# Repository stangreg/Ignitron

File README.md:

An ESP32 based foot pedal to communicate with the Spark Amp and Spark App via Bluetooth LE (iOS) and Bluetooth Serial (Android). Also works as a control device for a Looper app on the mobile. Ignitron also supports the built-in looper and additional HW presets of Spark 2.

**Ignitron has been successfully tested with**

* Spark 2
* Spark 40
* Spark Mini
* Spark GO
* **Spark NEO**

**Ignitron** gives you full control over your Spark Amp:
* Switch between the four **hardware presets**
* Switch between **custom saved presets** organized in banks
* **Toggle effects** for the selected preset
* **Save new presets** to Ignitron via the Spark App
* **Delete** stored presets
* Control the **Spark 2 internal looper**. 
* Control **Looper apps** on a mobile (actually *all* apps which support bluetooth keyboard controls)
* Use the built-in **Tuner**
* Show **Input Volume**
* Multiple BT keyboard layouts configurable

Adding new presets to **Ignitron** can easily be done as it can also act like a Spark Amp. Simply connect to **Ignitron** with the Spark App and save new presets directly from ToneCloud (or your downloaded presets) to **Ignitron**.

One big advantage of **Ignitron** is that it communicates with the Spark Amp using the **Bluetooth LE** protocol.
This means it is possible to connect your mobile to your Spark Amp as an audio speaker and play along your favorite songs while you control your effects with Ignitron.

The current active preset and effects are indicated via LEDs.\
In addition, the **built-in display** provides information on
* selected bank and preset number
* selected preset name
* operation mode (Preset, Manual/FX, Looper)
* activated pedal types in the FX chain
* Bluetooth connection status to Spark Amp and Spark App

This work was inspired by the [Sparkpal project](https://github.com/jamesguitar3/sparkpal), and the [Python Spark Parser project](https://github.com/paulhamsh/Spark-Parser) helped me to understand the messages being sent to and from the Spark Amp.

The following sections show how to [build](https://github.com/stangreg/SparkBLE#Building-Ignitron) and [operate](https://github.com/stangreg/SparkBLE#Operating-Ignitron) Ignitron.

Do you like my project? Then you can [buy me a coffee](https://ko-fi.com/stangreg)

# Building Ignitron
Software: [click here](https://github.com/stangreg/Ignitron/blob/main/src/)

Hardware: [click here](https://github.com/stangreg/Ignitron/blob/main/hardware/)

# Operating Ignitron

## Table of contents
* [Operation modes](https://github.com/stangreg/SparkBLE#operation-modes)
* [APP mode](https://github.com/stangreg/SparkBLE#app-mode)
* [Keyboard mode](https://github.com/stangreg/SparkBLE#keyboard-mode)
* [AMP mode](https://github.com/stangreg/SparkBLE#amp-mode)
  * [Storing a new preset](https://github.com/stangreg/SparkBLE#storing-a-new-preset-a-preset-from-the-app-needs-to-be-loaded)
  * [Deleting an existing preset](https://github.com/stangreg/SparkBLE#deleting-a-preset-only-possible-with-no-preset-from-the-app-loaded)
  * [Manually creating presets](https://github.com/stangreg/SparkBLE#manually-creating-presets)
    * [Preset format](https://github.com/stangreg/SparkBLE#preset-format)
    * [FX parameter reference](https://github.com/stangreg/SparkBLE#fx-parameter-reference)
* [OTA Update](https://github.com/stangreg/SparkBLE#OTA-Update)

## Operation modes
**Ignitron** has two operation modes, **APP mode** and **AMP mode**.\
In **APP mode** (default mode on startup), **Ignitron** connects to a Spark Amp and behaves like the Spark App towards the Spark Amp. It can then be used to switch between saved presets, toggle FX pedals, and even connect it to a Looper app on a mobile (providing 6 buttons to control a (looper or tabs) app).

**AMP mode** can be used to manage the presets stored on **Ignitron**, presets can be saved via the app or be deleted from **Ignitron**. For Android, the Bluetooth mode has to be set to Serial (SRL), for iOS it has to be set to BLE.\

**Keyboard mode** is useful when Ignitron should act as a bluetooth keyboard control without controlling a Spark Amp. This provides 2x6=12 buttons to control any supporting app (e.g., a looper or a tabs app).

To enter **AMP mode**, hold the `Preset 1` button during startup.
To enter **Keyboard mode**, hold the `Preset 3` button during startup.

Amp mode and Keyboard mode can best be started by holding the respective button pressed while pressing and holding `Preset 2` button to reset.

A graphical overview of all modes with button mapping can be found [here](https://github.com/stangreg/Ignitron/blob/main/resources/ignitron-cheatsheet.pdf). (Thanks to [@itarozzi](https://www.github.com/itarozzi) for creating this.)

## APP mode
In APP mode, the foot switches can be used to either switch between pre-saved presets (**Preset mode**), control all single effects in the selected preset (**Manual/FX mode**), or switch between presets while controlling an app on your mobile, e.g. a Looper app (**Looper (keyboard) mode**). If connected to a Spark 2 amp, the **Looper (amp) mode** will control the internal looper of the amp. You can easily toggle between **Preset mode** and **Manual/FX mode** by long pressing the `Bank-Up` button. To toggle between **Preset mode** and **Looper mode**, simply long-press the `Preset 4` button.

When selecting **Preset mode**, four buttons are used to select presets, the other two buttons are used to navigate through the preset banks. This way the user has access to a huge number of saved presets. When pressing the foot switch of the current active preset, the effect configured in the DRIVE section can be toggled.\
In **Manual/FX mode**, the user has direct access to all effects of the selected preset. Pressing a switch will toggle the respective FX type.\
When the **Tuner** is switched on, the output is shown on the display and the LEDs, allowing for quick tuning while connected with the amp.\
When **Looper (Keyboard) mode** is activated, Ignitron acts partially like a bluetooth keyboard. You can use the buttons to control a looper app, e.g. Loopy HD, and also switch between stored presets by long pressing the `Bank down`/`Bank up` buttons. **Note:** When switching presets in Looper mode, it will do this across banks.  
When **Looper (Amp) mode** is activated, Ignitron will control the internal looper of the Spark 2 amp. The display will also show information on the looper settings and click. The amp looper settings can easily be changed using Ignitron.

### Button commands in APP mode:

#### Preset mode
|Button      | Press pattern | Function           |
|----------- | :-----------: | ------------------ |
|`Bank down` | Short         | Navigate bank up   |
|`Bank up`   | Short         | Navigate bank down |
|`Preset 1`  | Short         | Select preset 1 / Toggle Drive |
|`Preset 2`  | Short         | Select preset 2 / Toggle Drive |
|`Preset 3`  | Short         | Select preset 3 / Toggle Drive |
|`Preset 4`  | Short         | Select preset 4 / Toggle Drive |
|`Preset 4` | Long           | Switch to Looper mode |
|`Bank down`   | Long          | Switch to Tuner mode. Short press while in Tuner mode to switch back to Preset mode.  |
|`Bank up`   | Long          | Switch to FX mode  |
|`Preset 2`  | Long          | Restart **Ignitron**  |

#### Manual/FX mode
|Button      | Press pattern | Function              |
|----------- | :-----------: | --------------------- |
|`Bank down` | Short         | Toggle Noise Gate     |
|`Bank up`   | Short         | Toggle Compressor/Wah |
|`Preset 1`  | Short         | Toggle Drive          |
|`Preset 2`  | Short         | Toggle Modulation     |
|`Preset 3`  | Short         | Toggle Delay          |
|`Preset 4`  | Short         | Toggle Reverb         |
|`Bank up`   | Long          | Switch to Preset mode |
|`Preset 2`  | Long          | Restart **Ignitron**  |

#### Looper (keyboard) mode (combined with Preset functionality)
|Button      | Press pattern | Function           |
|----------- | :-----------: | ------------------ |
|`Preset 1`  | Short         | Sends character "1" (can be freely configured in app) |
|`Preset 2`  | Short         | Sends character "2" (can be freely configured in app) |
|`Preset 3`  | Short         | Sends character "3" (can be freely configured in app) |
|`Preset 4`  | Short         | Sends character "4" (can be freely configured in app) |
|`Bank down` | Short         | Sends character "5" (can be freely configured in app) |
|`Bank up`   | Short         | Sends character "6" (can be freely configured in app) |
|`Bank down` | Long          | Switch to previous preset (across banks)  |
|`Bank up` | Long          | Switch to next preset (across banks)  |
|`Preset 4` | Long          | Switch to Preset mode |
|`Preset 2`  | Long          | Restart **Ignitron**     |

***Note:*** *In Looper mode, Ignitron is connected to your mobile as a bluetooth keyboard. If supported by the respective app on the mobile, the buttons can be freely configured to any function offered by the respective App. You may need to manually connect to the Ignitron BLE keyboard in your Bluetooth settings after switching to Looper mode.*

Example Button setup (available commands depend on availability in the respective app):
|Button      | Function           |
|----------- | ------------------ |
|`Preset 1`  | Record/overdub current track |
|`Preset 2`  | Play/pause session |
|`Preset 3`  | Delete current track (press twice) |
|`Preset 4`  | Mute current track |
|`Bank down` | Switch to previous track |
|`Bank up`   | Switch to next track |

#### Looper (amp) mode (to control the Spark 2 looper)
The preset buttons 1-3 mimick the three looper buttons on the amp, the LED status should match the LEDs on the amp.
With long pressing the `Bank up` button, Ignitron will toggle between Looper control mode and Looper config mode. The current mode will be shown by a 'L' or 'C' in the display respectively.

**Looper control mode**
|Button      | Press pattern | Function           |
|----------- | :-----------: | ------------------ |
|`Preset 1`  | Short         | Record / Dub |
|`Preset 2`  | Short         | Play / Stop |
|`Preset 3`  | Short         | Undo / Redo |
|`Preset 4`  | Short         | Read current Record status from amp (only needed for analysis) |
|`Bank down` | Short         | Tap tempo (repeatedly press button to adjust the tempo) |
|`Bank up`   | Short         | Read current looper settings from amp (only needed for analysis) |
|`Preset 3` | Long          | Delete all loops (reset)  |
|`Bank up` | Long          | Change to **Looper Config** mode  |
|`Preset 4` | Long          | Switch to Preset mode |
|`Preset 2`  | Long          | Restart **Ignitron**     |

**Looper config mode**
|Button      | Press pattern | Function           |
|----------- | :-----------: | ------------------ |
|`Preset 1`  | Short         | Change number of bars to be recorded |
|`Preset 2`  | Short         | Change feel of loop (straight / shuffle) |
|`Preset 3`  | Short         | Enable / Disable click |
|`Preset 4`  | Short         | NO FUNCTION |
|`Bank down` | Short         | Tap tempo (repeatedly press button to adjust the tempo) |
|`Bank up`   | Short         | NO FUNCTION |
|`Bank up` | Long          | Change to **Looper Control** mode  |
|`Preset 4` | Long          | Switch to Preset mode |
|`Preset 2`  | Long          | Restart **Ignitron**     |

-----------------------------------------------

## Keyboard mode
This mode will turn the Ignitron into a Bluetooth LE keyboard. All buttons will act like keyboard presses, there is no functionality regarding Preset change or other Spark Amp related functions. Use this mode if you want to only use Ignitron as a looper control device (or any other supporting app like a tabs app) . If you want to use looper control in combination with Spark Amp control, use the Looper mode as part of the APP mode (see above).
In the code, multiple different keyboard layouts can be defined to support various apps. In operations, Ignitron can switch between these keyboard with the press of a button.

Every key needs be configured with the following parameters:
- *Key ID* (1-6 for short presses, 11-14 for long presses)
- *Key code*
- *Modifier key* (Shift, CTRL, etc.)
- Key press *repetitions* (0 for single press)
- *String representation* of key in display (should only be 1 character)

In operations, when a button is pressed, the corresponding key including modifiers will be sent to the connected device. The display will show the key representations of the currently active keyboard.
The standard defined keyboard layout will send characters `1` to `6` for short presses and characters `A` to `D`for long presses.

Example:
```
{
  1,
  0xD8, // KEY_LEFT_ARROW
  0x81, // KEY_LEFT_SHIFT
  2,
  "<"
}
```
   
If a key is configured like the above, a button press will send the combination of the `LEFT SHIFT` and `LEFT ARROW` keys with 2 repetitions. In the display the key will be shown as `<`.
Long pressing `Bank down` and `Bank up` are reserved for keyboard layout switching.

Key codes for special keys can be found here: [BLE Keyboard Library](https://github.com/T-vK/ESP32-BLE-Keyboard/blob/master/BleKeyboard.h)

In keyboard mode, the following keys will be sent to the connected device:

|Button      | Press pattern | Function           |
|----------- | :-----------: | ------------------ |
|`Preset 1`  | Short         | Sends defined character (function can be freely configured in app) |
|`Preset 2`  | Short         | Sends defined character (function can be freely configured in app) |
|`Preset 3`  | Short         | Sends defined character (function can be freely configured in app) |
|`Preset 4`  | Short         | Sends defined character (function can be freely configured in app) |
|`Bank down` | Short         | Sends defined character (function can be freely configured in app) |
|`Bank up`   | Short         | Sends defined character (function can be freely configured in app) |
|`Preset 1`  | Long          | Sends defined character (function can be freely configured in app) |
|`Preset 2`  | Long          | Sends defined character (function can be freely configured in app) |
|`Preset 3`  | Long          | Sends defined character (function can be freely configured in app) |
|`Preset 4`  | Long          | Sends defined character (function can be freely configured in app) |
|`Bank down` | Long          | Switch to previous keyboard layout (cycling) |
|`Bank up`   | Long          | Switch to next keyboard layoout (cycling) |

-----------------------------------------------

## AMP mode
In AMP mode, **Ignitron** acts like a Spark AMP and can communicate with the Spark app running on a mobile. New presets can be stored on **Ignitron** and existing presets can be deleted.

### Connecting the Spark app with **Ignitron**

***Note:*** By default, Ignitron is configured to use BLE which only works with iOS. In order to connect an Android device, you need to switch to Serial Bluetooth. To do so, press and hold the `Bank Up` button when in AMP mode (after step 1. below). This will toggle the Bluetooth mode and restart **Ignitron**. After toggling the Bluetooth mode, start with step 1. below again. Ignitron persists the Bluetooth mode over restarts.  

1. Start **Ignitron** in AMP mode (hold `Preset 1` button during startup).
2. Open the Spark App on the mobile
3. For the first connection, make sure to have your real Spark Amp powered off to avoid the app connecting to it.
4. Hit the connect button in the app (or the + button in the connection overview)
5. Once the connection is established, you can give the connection a name in the app so you can distinguish from your regular Spark Amp connection.

### Storing a new preset (a preset from the app needs to be loaded)
1. Start **Ignitron** in AMP mode (hold Preset 1 button during startup).
2. Connect the Spark App with **Ignitron** (see above)
3. Select a preset in the app (either saved in the app or from ToneCloud).
4. The preset name should appear in the bottom line of the display
5. The `Preset`/`Bank` buttons on **Ignitron** can be used to navigate to the desired preset position.
6. Press the `Preset` button to mark the position for storing *(the LED of the selected preset position should start blinking)*
7. Hit the same `Preset` button a second time to confirm storage
(Hitting any other `Preset`/`Bank` button will revert the state back to navigating)
8. The preset will be saved to the selected position, other presets will be pushed one position back

#### Button commands (case: preset has been received from Spark app)
| Button     | Press pattern | Function                        | Remark |
| ---------- | :-----------: | ------------------------------- | ------ |
|`Bank down` | Short         | Navigate bank up                |        |
|`Bank up`   | Short         | Navigate bank down              |        |
|`Preset 1`  | Short         | Select preset 1                 | *Press twice to store received preset* |
|`Preset 2`  | Short         | Select preset 2                 | *Press twice to store received preset* |
|`Preset 3`  | Short         | Select preset 3                 | *Press twice to store received preset* |
|`Preset 4`  | Short         | Select preset 4                 | *Press twice to store received preset* |
|`Bank down` | Long          | Unload preset                   | *Removes loaded preset if present*     |
|`Bank up`   | Long          | Toggle Bluetooth mode                   | *Toggle between BLE and BT Serial mode*  |
|`Preset 2`  | Long          | Restart **Ignitron**                  |        |

### Deleting a preset (only possible when no preset from the app is loaded)
1. Start **Ignitron** in AMP mode (hold `Preset 1` button during startup).
2. Use the `Preset`/`Bank` buttons on **Ignitron** to navigate to the desired preset position
3. **Long press** the `Bank Down` button to mark the selected preset for deletion
4. The LED of the selected preset should start blinking
5. In the display you should see a prompt if deletion should be executed
6. If you want to cancel the deletion, simply short press any other button
7. Otherwise, **long press** the `Bank Down` button again to confirm deletion.
(Hitting any other button will cancel the deletion and return back to navigation)

#### Button commands (case: no preset has been received, slot is empty)
| Button     | Press pattern | Function                 | Remark |
| ---------- | :-----------: | ------------------------ | ------ |
|`Bank down` | Short         | Navigate bank up         |        |
|`Bank up`   | Short         | Navigate bank down       |        |
|`Preset 1`  | Short         | Select preset 1          |        |
|`Preset 2`  | Short         | Select preset 2          |        |
|`Preset 3`  | Short         | Select preset 3          |        |
|`Preset 4`  | Short         | Select preset 4          |        |
|`Bank down` | Long          | Mark preset for deletion | *Pressing any other button in that state will cancel the deletion* |
|`Bank down` | Long          | Delete marked preset     | *Only if preset was first marked for deletion* |
|`Bank up` | Long          | Toggle Bluetooth mode                   | *Toggle between BLE and BT Serial mode*  |
|`Preset 2`  | Long          | Restart **Ignitron**           |        |

-------------------------------------------------------

### Manually creating presets
*This method is only recommended if a preset cannot be transferred via the Spark app or if the preset files have been received/generated in a different way.*
1. Create a **preset file** in JSON format as shown below
2. Make sure the **file name** does not exceed 31 characters (including the `.json` suffix)
3. Put the file name into the **data folder**
4. Insert the file name (including the `.json` suffix) to the desired prefix location in the `PresetList.txt` file
5. *Place the PresetList.txt file into the data folder (if not already there)*
6. **Upload the data folder** to **Ignitron** via the Arduino IDE (or other tools)

#### Preset format
**Ignitron** stores presets in a JSON format using the SPIFFS file system.
Each preset is stored in a separate file and presets are organized in a separate text file called 'PresetList.txt'. This list simply stores the file names of the presets, the order defines the way the banks are filled.
An example preset file would look like this:
```
{"PresetNumber": 127, "UUID":"DEFBB271-B3EE-4C7E-A623-2E5CA53B6DDA",
"Name":"Studio Session" , "Version":"0.7", "Description":"Description for Acoustic Preset 1", "Icon":"icon.png", "BPM": 120.0000,
"Pedals": [
  { "Name":"bias.noisegate",  "IsOn": false,  "Parameters":[0.5000,0.3467] },
  { "Name":"BBEOpticalComp",  "IsOn": true,   "Parameters":[0.7583,0.2585,0.0000] },
  { "Name":"DistortionTS9",   "IsOn": false,  "Parameters":[0.1396,0.4073,0.6898] },
  { "Name":"Acoustic",  "IsOn": true,   "Parameters":[0.6398,0.3851,0.3834,0.5994,0.5195] },
  { "Name":"ChorusAnalog",  "IsOn": true,   "Parameters":[0.8417,0.2275,0.9359,0.3513] },
  { "Name":"DelayMono",   "IsOn": false,  "Parameters":[0.2240,0.2112,0.4909,0.6000,1.0000] },
  { "Name":"bias.reverb",   "IsOn": true,   "Parameters":[0.7228,0.3262,0.2758,0.3607,0.3439,0.4860,0.4000] } ],
"Filler":"23"
}
```

As a guidance which effect and amp names can be used and in which order the parameters of each effect have to be given, please see below.

#### FX parameter reference
In order to know which effects are available with paramters, see below table.
This data can be used to build own presets in JSON format (see above).
Use the Technical Name information in the JSON files.
Parameters marked with `Switch` can only have values of 0 or 1, others can have any value between 0 and 1.

##### Standard Tones

| Type       | App&nbsp;Name           | Technical&nbsp;Name&nbsp;(JSON)    | Parameter&nbsp;0             | Parameter&nbsp;1             | Parameter&nbsp;2         | Parameter&nbsp;3    | Parameter&nbsp;4  | Parameter&nbsp;5 | Parameter&nbsp;6         | Extra&nbsp;Info                    |
|------------|--------------------|-------------------|-------------------------|-------------------------|---------------------|----------------|--------------|-------------|---------------------|-------------------------------|
| Noise Gate | Noise Gate         | bias.noisegate    | Threshold               | Decay                   |                     |                |              |             |                     |                               |
| Compressor | LA Comp            | LA2AComp          | Limit/Compress `Switch` | Gain                    | Peak Reduction      |                |              |             |                     |                               |
| Compressor | Sustain Comp       | BlueComp          | Level                   | Tone                    | Attack              | Sustain        |              |             |                     |                               |
| Compressor | Red Comp           | Compressor        | Output                  | Sensitivity             |                     |                |              |             |                     |                               |
| Compressor | Bass Comp          | BassComp          | Comp                    | Gain                    |                     |                |              |             |                     |                               |
| Compressor | Optical Comp       | BBEOpticalComp    | Volume                  | Comp                    | Pad `Switch`        |                |              |             |                     |                               |
| Drive      | Booster            | Booster           | Gain                    |                         |                     |                |              |             |                     |                               |
| Drive      | Clone Drive        | KlonCentaurSilver | Output                  | Treble                  | Gain                |                |              |             |                     |                               |
| Drive      | Tube Drive         | DistortionTS9     | Overdrive               | Tone                    | Level               |                |              |             |                     |                               |
| Drive      | Over Drive         | Overdrive         | Level                   | Tone                    | Drive               |                |              |             |                     |                               |
| Drive      | Fuzz Face          | Fuzz              | Volume                  | Fuzz                    |                     |                |              |             |                     |                               |
| Drive      | Black Op           | ProCoRat          | Distortion              | Filter                  | Volume              |                |              |             |                     |                               |
| Drive      | Bass Muff          | BassBigMuff       | Volume                  | Tone                    | Sustain             |                |              |             |                     |                               |
| Drive      | Guitar Muff        | GuitarMuff        | Volume                  | Tone                    | Sustain             |                |              |             |                     |                               |
| Drive      | Bassmaster         | MaestroBassmaster | Brass Volume            | Sensitivity             | Bass Volume         |                |              |             |                     |                               |
| Drive      | SAB Driver         | SABDriver         | Volume                  | Tone                    | Drive               | LP/HP `Switch` |              |             |                     |                               |
| Amp        | Silver 120         | RolandJC120       | Gain                    | Treble                  | Middle              | Bass           | Volume       |             |                     |                               |
| Amp        | Black Duo          | Twin              | Gain                    | Treble                  | Middle              | Bass           | Volume       |             |                     |                               |
| Amp        | AD Clean           | ADClean           | Gain                    | Treble                  | Middle              | Bass           | Volume       |             |                     |                               |
| Amp        | Match DC           | 94MatchDCV2       | Gain                    | Treble                  | Middle              | Bass           | Volume       |             |                     |                               |
| Amp        | ODS 50             | ODS50CN           | Gain                    | Treble                  | Middle              | Bass           | Volume       |             |                     |                               |
| Amp        | Blues Boy          | BluesJrTweed      | Gain                    | Treble                  | Middle              | Bass           | Volume       |             |                     |                               |
| Amp        | Tweed Bass         | Bassman           | Gain                    | Treble                  | Middle              | Bass           | Volume       |             |                     |                               |
| Amp        | AC Boost           | AC Boost          | Gain                    | Treble                  | Middle              | Bass           | Volume       |             |                     |                               |
| Amp        | Checkmate          | Checkmate         | Gain                    | Treble                  | Middle              | Bass           | Volume       |             |                     |                               |
| Amp        | Two Stone SP50     | TwoStoneSP50      | Gain                    | Treble                  | Middle              | Bass           | Volume       |             |                     |                               |
| Amp        | American Deluxe    | Deluxe65          | Gain                    | Treble                  | Middle              | Bass           | Volume       |             |                     |                               |
| Amp        | Plexiglas          | Plexi             | Gain                    | Treble                  | Middle              | Bass           | Volume       |             |                     |                               |
| Amp        | JM45               | OverDrivenJM45    | Gain                    | Treble                  | Middle              | Bass           | Volume       |             |                     |                               |
| Amp        | Lux Verb           | OverDrivenLuxVerb | Gain                    | Treble                  | Middle              | Bass           | Volume       |             |                     |                               |
| Amp        | RB 101             | Bogner            | Gain                    | Treble                  | Middle              | Bass           | Volume       |             |                     |                               |
| Amp        | British 30         | OrangeAD30        | Gain                    | Treble                  | Middle              | Bass           | Volume       |             |                     |                               |
| Amp        | American High Gain | AmericanHighGain  | Gain                    | Treble                  | Middle              | Bass           | Volume       |             |                     |                               |
| Amp        | SLO 100            | SLO100            | Gain                    | Treble                  | Middle              | Bass           | Volume       |             |                     |                               |
| Amp        | YJM100             | YJM100            | Gain                    | Treble                  | Middle              | Bass           | Volume       |             |                     |                               |
| Amp        | Treadplate         | Rectifier         | Gain                    | Treble                  | Middle              | Bass           | Volume       |             |                     |                               |
| Amp        | Insane             | EVH               | Gain                    | Treble                  | Middle              | Bass           | Volume       |             |                     |                               |
| Amp        | Insane 6508        | 6505Plus          | Gain                    | Treble                  | Middle              | Bass           | Volume       |             |                     |                               |
| Amp        | SwitchAxe          | SwitchAxeLead     | Gain                    | Treble                  | Middle              | Bass           | Volume       |             |                     |                               |
| Amp        | Rocker V           | Invader           | Gain                    | Treble                  | Middle              | Bass           | Volume       |             |                     |                               |
| Amp        | BE 101             | BE101             | Gain                    | Treble                  | Middle              | Bass           | Volume       |             |                     |                               |
| Amp        | Pure Acoustic      | Acoustic          | Gain                    | Treble                  | Middle              | Bass           | Volume       |             |                     |                               |
| Amp        | Fishboy            | AcousticAmpV2     | Gain                    | Treble                  | Middle              | Bass           | Volume       |             |                     |                               |
| Amp        | Jumbo              | FatAcousticV2     | Gain                    | Treble                  | Middle              | Bass           | Volume       |             |                     |                               |
| Amp        | Flat Acoustic      | FlatAcoustic      | Gain                    | Treble                  | Middle              | Bass           | Volume       |             |                     |                               |
| Amp        | RB-800             | GK800             | Gain                    | Treble                  | Middle              | Bass           | Volume       |             |                     |                               |
| Amp        | Sunny 3000         | Sunny3000         | Gain                    | Treble                  | Middle              | Bass           | Volume       |             |                     |                               |
| Amp        | W600               | W600              | Gain                    | Treble                  | Middle              | Bass           | Volume       |             |                     |                               |
| Amp        | Hammer 500         | Hammer500         | Gain                    | Treble                  | Middle              | Bass           | Volume       |             |                     |                               |
| Modulation | Tremolo            | Tremolo           | Speed                   | Depth                   | Level               |                |              |             |                     |                               |
| Modulation | Chorus             | ChorusAnalog      | E.Level                 | Rate                    | Depth               | Tone           |              |             |                     |                               |
| Modulation | Flanger            | Flanger           | Rate                    | Mix                     | Depth               |                |              |             |                     |                               |
| Modulation | Phaser             | Phaser            | Speed                   | Intensity               |                     |                |              |             |                     |                               |
| Modulation | Vibrato            | Vibrato01         | Speed                   | Depth                   |                     |                |              |             |                     |                               |
| Modulation | UniVibe            | UniVibe           | Speed                   | Vibrato/Chorus `Switch` | Intensity           |                |              |             |                     |                               |
| Modulation | Cloner Chorus      | Cloner            | Rate                    | Depth `Switch`          |                     |                |              |             |                     |                               |
| Modulation | Classic Vibe       | MiniVibe          | Speed                   | Intensity               |                     |                |              |             |                     |                               |
| Modulation | Tremolator         | Tremolator        | Depth                   | Speed                   | BPM On/Off `Switch` |                |              |             |                     |                               |
| Modulation | Tremolo Square     | TremoloSquare     | Speed                   | Depth                   | Level               |                |              |             |                     |                               |
| Modulation | Guitar EQ          | GuitarEQ6         | Level                   | 100                     | 200                 | 400            | 800          | 1.6k        | 3.2k                |                               |
| Modulation | Bass EQ            | BassEQ6           | Level                   | 50                      | 120                 | 400            | 800          | 4.5k        | 10k                 |                               |
| Delay      | Digital Delay      | DelayMono         | E.Level                 | Feedback                | DelayTime           | Mode           | BPM `Switch` |             |                     | Modes: 0.3 (50ms) - 0.4 (200ms) - 0.6 (500ms) - 0.72 (1s) |
| Delay      | Echo Filt          | DelayEchoFilt     | Delay                   | Feedback                | Level               | Tone           | BPM `Switch` |             |                     |                               |
| Delay      | Vintage Delay      | VintageDelay      | Repeat Rate             | Intensity               | Echo                | BPM `Switch`   |              |             |                     |                               |
| Delay      | Reverse Delay      | DelayReverse      | Mix                     | Decay                   | Filter              | Time           | BPM `Switch` |             |                     |                               |
| Delay      | Multi Head         | DelayMultiHead    | Repeat Rate             | Intensity               | Echo Volume         | Mode Selector  | BPM `Switch` |             |                     | Modes: 0 (Head 1) - 0.35 (Head 2) - 0.65 (Head 3) - 0.95 (Head 4) |
| Delay      | Echo Tape          | DelayRe201        | Sustain                 | Volume                  | Tone                | Short/Long     |              |             |                     |                               |
| Reverb     | Room Studio A      | bias.reverb       | Level                   | Damping                 | Dwell               | Time           | Low Cut      | High Cut    | Selects Reverb Type | 0.0                           |
| Reverb     | Room Studio B      | bias.reverb       | Level                   | Damping                 | Dwell               | Time           | Low Cut      | High Cut    | Selects Reverb Type | 0.1                           |
| Reverb     | Chamber            | bias.reverb       | Level                   | Damping                 | Dwell               | Time           | Low Cut      | High Cut    | Selects Reverb Type | 0.2                           |
| Reverb     | Hall Natural       | bias.reverb       | Level                   | Damping                 | Dwell               | Time           | Low Cut      | High Cut    | Selects Reverb Type | 0.3                           |
| Reverb     | Hall Medium        | bias.reverb       | Level                   | Damping                 | Dwell               | Time           | Low Cut      | High Cut    | Selects Reverb Type | 0.4                           |
| Reverb     | Hall Ambient       | bias.reverb       | Level                   | Damping                 | Dwell               | Time           | Low Cut      | High Cut    | Selects Reverb Type | 0.5                           |
| Reverb     | Plate Short        | bias.reverb       | Level                   | Damping                 | Dwell               | Time           | Low Cut      | High Cut    | Selects Reverb Type | 0.6                           |
| Reverb     | Plate Rich         | bias.reverb       | Level                   | Damping                 | Dwell               | Time           | Low Cut      | High Cut    | Selects Reverb Type | 0.7                           |
| Reverb     | Plate Long         | bias.reverb       | Level                   | Damping                 | Dwell               | Time           | Low Cut      | High Cut    | Selects Reverb Type | 0.8                           |

##### Hendrix Tones
**Note:** You can simply store tones using Hendrix gear on Ignitron. As the effects are licensed and purchased In-App, you need to connect your mobile Spark App to the Spark Amp after switching on the Spark Amp. When you then disconnect the Spark App and connect Ignitron afterwards you should be able to use presets using below gear.

| Type       | App&nbsp;Name           | Technical&nbsp;Name    | Parameter&nbsp;0             | Parameter&nbsp;1             | Parameter&nbsp;2         | Parameter&nbsp;3    | Parameter&nbsp;4  | Parameter&nbsp;5 | Parameter&nbsp;6         | Extra&nbsp;Info                    |
|------------|--------------------|-------------------|-------------------------|-------------------------|---------------------|----------------|--------------|-------------|---------------------|-------------------------------|
| Compressor/Wah | J.H. Legendary Wah         | JH.Vox846    | Auto Wah Mode               | BPM Mode `Switch`                  |  ms (BPM Off)                   | Bar (BPM On)               | Sensitivity             |             |                     | Auto Wah Mode: 0.0, 0.2, 0.4, 0.6, 0.8, 1.0 - Bar: 0.0 (1/8), 0.25 (1/4), 0.5 (1/2), 0.75 (1/1)                              |
| Drive | J.H. Axle Fuzz           | JH.AxisFuzz          | Volume | Drive                    |             |                |              |             |                     |                               |
| Drive | J.H. Super Fuzz      | JH.SupaFuzz          | Volume                   | Filter                    |               |         |              |             |                     |                               |
| Drive | J.H. Octave Fuzz           | JH.Octavia        | Level                  | Fuzz             |                     |                |              |             |                     |                               |
| Drive | J.H. Fuzz Zone          | JH.FuzzTone          | Volume                    | Attack                    |                     |                |              |             |                     |                               |
| Modulation/EQ | J.H. Legendary Vibe      | JH.VoodooVibeJr    | Speed                  | Sweep                    | Intensity        | Mix (Vibrato/Chorus)               |              |             |                     |                               |

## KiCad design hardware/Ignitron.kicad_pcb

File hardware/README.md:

# Ignitron - Hardware
This document describes the hardware side of the **Ignitron** foot pedal.

The software that controls the Spark amp runs on an ESP32 microcontroller which needs to be connected to the actual hardware so that it's able to react to hardware events, e.g. foot switch presses, and to indicate the current state via the LEDs. All of these connections, except the power supply via USB, are made via a PCB that piggybacks onto the ESP32 board.

One objective of the PCB design was to keep things as modular as possible. This means that no cables coming from the hardware should be soldered directly to the PCB or the ESP32. For example the foot switches, LEDs and the external power supply are supposed to be connected by PCB connectors that can be connected and disconnected. In case you cannot find such connectors you can of course still solder the cables directly to the PCB.

## Bill of Materials (BOM)
To keep things clean the bill of materials will differentiate between hardware like the enclosure, switches, etc. and everything that's needed to assemble the PCB.

### Hardware
|Component|Quantity|Comment|
|---|:---:|---|
|[ESP32](https://www.berrybase.de/dev.-boards/esp8266-esp32-d1-mini/boards/esp32-nodemcu-development-board)|1|Make sure that the dimensions and pin order matches with the PCB (details below).
|[SSD1306 OLED Display 128x64 0.96"](https://www.amazon.de/AZDelivery-Display-Arduino-Raspberry-gratis/dp/B074N9VLZX)|1|Make sure that the dimensions of the display you choose fit the OLED frame!
|[1590DD Enclosure](https://www.taydaelectronics.com/hardware/enclosures/1590dd-style/matte-black-1590dd-style-aluminum-diecast-enclosure.html)|1|
|[SPST Momentary Footswitch](https://www.taydaelectronics.com/spst-momentary-soft-touch-push-button-stomp-foots-pedal-switch.html)|6|
|[LED 5mm](https://www.taydaelectronics.com/leds/round-leds/5mm-leds.html)|6|
|[LED Holder](https://www.reichelt.de/einbaufassung-fuer-5-mm-leds-aussenreflektor-chrom-ebf-a-5-p7288.html?&trstct=pol_3&nbc=1)|6|
|[DC Power Jack](https://www.taydaelectronics.com/hardware/dc-power/dc-power-jack-2-1mm-enclosed-frame-with-switch-red.html)|1|Optional if you only want to power via USB using the adapter.|
|[USB Adapter Cliff CP30208N](https://www.reichelt.de/usb-adapter-ft-1-x-usb-2-0-a-buchse-1-x-usb-2-0-a-buchse-cliff-cp30208n-p227645.html)|1|Optional if you only want to power using the DC power jack.
|USB A to Micro USB Cable|1|Optional if you only want to power using the DC power jack.
|OLED Frame|1|Details below.

### PCB
The PCB is provided as a KiCad PCB project ([Ignitron.kicad_pcb](Ignitron.kicad_pcb)) and must be manufactured at a service that supports [KiCad](https://www.kicad.org/) projects. This can for example be [OSH Park](https://oshpark.com/) (if you are located in the USA), [Aisler](https://aisler.net/) (if you are located in Europe). Just download the PCB project [Ignitron.kicad_pcb](Ignitron.kicad_pcb) from this site and and upload it to the service that you want to use.

The schematics for the PCB can be found [here](Ignitron-Schematics.pdf).

To populate the PCB itself you will need the following components:

|Ref|Quantity|Component|Value|Comment|
|:---:|:---:|---|:---:|---|
|D1, D2, D3, D4, D5, D6|6|[PCB connector with two pins](https://www.reichelt.de/platinensteckverbinder-gerade-weiss-2-polig-ps-25-2g-ws-p14825.html)|-|Alternatively connect the LEDs directly with cables|
|SW1, SW2, SW3, SW4, SW5, SW6|6|[PCB connector with two pins](https://www.reichelt.de/platinensteckverbinder-gerade-weiss-2-polig-ps-25-2g-ws-p14825.html)|-|Alternatively connect the switches directly with cables|
|J1|1|[PCB connector with two pins](https://www.reichelt.de/platinensteckverbinder-gerade-weiss-2-polig-ps-25-2g-ws-p14825.html)|-|Alternatively connect the power jack directly with a cable|
|J2|1|[1x4 angled pin header](https://www.taydaelectronics.com/connectors-sockets/pin-headers/40-pin-2-54-mm-angle-single-row-pin-header.html)|-|For the connection of the OLED display. Solder to lower side to be able to read the values on the top|
|IC1|2|[1x19 female pin header](https://www.taydaelectronics.com/connectors-sockets/pin-headers/20-pin-2-54-mm-single-row-female-pin-header.html)|-|If possible get two 1x19 headers. Otherwise use 1x20 headers and cut off the unused leg.|
|R1, R2, R3, R4, R5, R6|6|¼ W Resistor|470R|Resistors for the "Drive" (R1), "Mod" (R2), "Delay" (R3), "Reverb" (R4), "Noise Gate" (R5) and "Comp" (R6) LEDs. Match with the actual LEDs.|
|R7, R8, R9, R10, R11, R12|6|¼ W Resistor|1K|Resistors for the switches|

### OLED Frame
The OLED frame was designed with [OpenSCAD](https://openscad.org/). The project file is [tinyOledBezel.scad](tinyOledBezel.scad) which is an adjusted version of [this design](https://www.thingiverse.com/thing:1645893).

The final STL file that can be printed at a 3D printing service is [tinyOledBezel.stl](tinyOledBezel.stl). If you are located in Germany you can for example get it printed at [FDM Druckservice](https://fdm-druckservice.de/produkt/fdm-designer).

The design consists of the actual frame and two bars that can be used to hold the display in place. Snap off the bars and the connector so that you are left with the frame and the two bars.

# Enclosure
The following assumes that the enclosure will be ordered at Tayda Electronics. Order the following hardware/services on their [main page](https://www.taydaelectronics.com/).
* A 1590DD enclosure. The pictures show a [matte black](https://www.taydaelectronics.com/hardware/enclosures/1590dd-style/matte-black-1590dd-style-aluminum-diecast-enclosure.html) enclosure.
* [Drill service](https://www.taydaelectronics.com/hardware/enclosures/enclosure-custom-drill-service/1590dd-custom-drill-enclosure-service.html)
* [UV printing service](https://www.taydaelectronics.com/hardware/enclosures/enclosure-uv-printing-service/1590dd-uv-printing-service.html)
* [Gloss layer](https://www.taydaelectronics.com/hardware/enclosures/enclosure-uv-printing-service/custom-uv-gloss-layer-service.html)

Once you have ordered the items listed above go to [Tayda Tool Box](https://drill.taydakits.com) page and create a drill and print template.

## Drill template
Setup a drill template with the following holes:
|Element|Side|Diameter (mm)| X Position (mm)|Y Position (mm)|
|---|:---:|:---:|:---:|:---:|
|LED Drive|A|8.2|10|-75|
|LED Mod|A|8.2|10|-25|
|LED Delay|A|8.2|10|25|
|LED Reverb|A|8.2|10|75|
|LED Noise|A|8.2|-47|25|
|LED Comp|A|8.2|-47|75|
|Switch Drive|A|12.2|36.5|-75|
|Switch Mod|A|12.2|36.5|-25|
|Switch Delay|A|12.2|36.5|25|
|Switch Reverb|A|12.2|36.5|75|
|Switch Noise|A|12.2|-20.5|25|
|Switch Comp|A|12.2|-20.5|75|
|Display Large|A|32.2|-20.5|-64.2|
|Display Small 1|A|5.4|-7.2|-50.9|
|Display Small 2|A|5.4|-33.8|-50.9|
|Display Small 3|A|5.4|-33.8|-77.5|
|Display Small 4|A|5.4|-7.2|-77.5|
|USB Body|C|24.2|0|50|
|USB Screw 1|C|3|-9.5|62|
|USB Screw 2|C|3|9.5|38|
|Power|C|12.2|0|-75|

## UV print
Download [Ignitron-UV-Print.pdf](Ignitron-UV-Print.pdf) from this site and upload it as a UV print template at the [Tayda Tool Box](https://drill.taydakits.com).

⚠️ Please note that you must use a PDF viewer that supports layers if you want to take a look at the PDF on your computer. Otherwise you will likely only see the GLOSS layer which covers the actual design. If you open the PDF with a recent version of Firefox you should be able to switch the layers on and off.

## Connect the drill and design template with the order
A few minutes after you have placed your order at Tayda it should be possible to connect the services from your order with the templates that you have just created. Follow the instructions on the [Tayda Tool Box](https://drill.taydakits.com) page.

# Assembly
The following assumes that you have received the UV printed and drilled enclosure from Tayda and that you have everything else from the BOM.

## Enclosure preparation
The display (frame) needs a rectangular hole in the enclosure but unfortunately it is not possible to order rectangular holes at Tayda Electronics. Therefore it is necessary to manually file away the excess material that could not be removed by the round drills in the area of the display hole. Try to file away only so much material that the OLED frame fits and can be snapped into the hole without having to glue anything. Also make sure that the enclosure is not scratched by scrap material.
1. Cover the whole enclosure except for the display hole area with tape.
2. File away the excess material. If you have used the provided enclosure design then the area where the display will be located is printed in white. File away (almost) all white material in that case.
3. Once you have made sure that the OLED frame fits carefully remove the tape and clear the enclosure, e.g. by holding it under running water. Make sure that the enclosure is not scratched by scrap material!

## PCB assembly
Follow these steps to solder the PCB:
1. Solder the resistors R1 - R6. These are for the LEDs and you might need to adjust their values to adjust the brightness of the chosen LEDs.
2. Solder the resistors R7 - R12. These are all 1 K resistors for the switches.
3. Solder the receiving ends of the PCB connectors D1 - D6, SW1 - SW6 and J1.
4. Solder the two 1x19 female pin headers. Please note that these go on the "lower" side of the board that says "IC1"! In general make sure that they are soldered in such a way that you can connect corresponding pins on the ESP32 and the PCB, i.e. 3V3 goes to 3V3, GND goes to GND, etc.
To make sure that the headers fit well on the ESP32 once they are soldered to the PCB you can lay the ESP32 on it's back, put the two headers on it and then put the PCB on top of that to solders the first few points. If you need to use 1x20 headers the two excess pins will be in the area of the 3V3 and GND pin. Snap their electrical contacts once you have soldered the headers to the board.
6. Solder the 1x4 angled pin header to J2. Attach it to the "lower" side of the board so that you can still read the values on the "upper" side of the board.

## Final assembly
Once the enclosure is prepared and the PCB is assembled we can finally put everything together. On the [main page](https://www.github.com/stangreg/Ignitron) you can find an image that shows how everything is fit into the enclosure and what goes where.
1. Put the OLED display into the OLED frame, secure it with the bars and put the frame with the display into the enclosure.
2. Put some insulating tape in the area where the ESP32 with the attached PCB will go.
3. Install the LEDs and switches into the enclosure and measure how long the cables of the PCB connectors must be for each of them so they reach the PCB. Please refer to the resistor listings for R1 - R6 in the PCB BOM on how the numbers are mapped to "Drive", "Mod", etc. Example: SW1 refers to the switch for "Drive", D1 refer to the LED for "Drive".
4. Take out the switches again to make it easier to solder them later. Keep the LEDs inside because you will need to solder them in an installed state anyway.
5. Install the USB adapter if you want to use it.
6. Solder the PCB connectors to the switches. The order of the cables does not matter in this case.
7. Solder the PCB connectors to the installed LEDs.
⚠️ Please note that the order matters in this case because the connector will only connect to the receiver in one way! If you connect it the wrong way then the LEDs will not light up.
8. Solder the PCB connector to the power jack if you want to use it.
⚠️ As with the LEDs order matters here!
10. Install the switches into the enclosure again.
11. Install the power jack if you want to use it.
12. Connect the LEDs correctly to D1 - D6, the switches to SW1 - SW6 and the power jack to J1.
13. Connect the display to the PCB.
14. Use the USB A to Micro-USB cable to connect the adapter to the ESP32.
15. Close the enclosure.

Test everything.

## Additional Features

### Battery Indicator

Starting from version 1.7.2, Ignitron can be powered by an internal battery pack and displays the remaining capacity on the LED screen.

This section explains how to build the hardware for this feature. To enable it in software, see [this guide](../src/Readme.md#battery-indicator).

#### BOM

| Component         | Quantity | Comment                                      |
|-------------------|:--------:|----------------------------------------------|
| 5.5*2.1 DC Jack   | x        | Optional. To power other pedals.             |
| 5.1k resistor     | 1        | For voltage divider.                         |
| 15k resistor      | 1        | For voltage divider.                         |
| Battery pack      | 1        | Supports 2S and 3S Li-ion or LiFePO4 packs.  |
| LDO module, e.g., LM317 | x  | Optional. To reduce voltage for pedals.      |
| AMS1117 5.0       | 1        | For powering ESP32.                          |
| Power switch      | 1        | Power switch.                                |

Choose the battery pack: If your pedals require 9V, a 2S Li-ion pack is a good choice as it matches the discharge profile of a 9V alkaline battery. For 12V pedals, use a 3S Li-ion pack and add an LDO to reduce the output voltage to 9V for 9V pedals. If you don't need power output, choose any battery that provides more than 5V.

Why use a 2S/3S battery pack with an LDO instead of a 1S battery with a voltage booster? LDOs do not introduce audible buzz like voltage boost chips, although they waste more energy as heat.

#### Connection

See [Ignitron-Battery-Indicator-Schematics.pdf](./Ignitron-Battery-Indicator-Schematics.pdf) for details.

### 3D Printed case

Link to Thingiverse: [Ignitron case - foot pedal for Positive Grid Spark amps](https://www.thingiverse.com/thing:6952547)

A 3D printed case that is custom made for **Ignitron** is contributed by user @Barsk (orginal design by @Intaker). Note that the design is made for a 1.3" OLED display (original design uses 0.96") and a 38 pin ESP32 devkit board featuring four mounting holes. There are many clones and any with the same dimension will do. A version without the holes *may* work, it is untested though and migh t need some hot glue perhaps for mounting. 

The case is designed to power the ESP32 board directly by its own USB port, which is available from a port in the outer casing. 

The case is made with an internal part that needs to be printed with a translucent filament so the LEDs can shine through. Natural PLA (uncolored transparent) works fine, transparent PETG is an option. The outer shell should be printed in an opaque color of choice. It is easy to print outer shells in various colors and change the "skin" of the Ignatron. The texts for TUNER, MAN FX, AMP, Reboot icon, LOOPER and Bank Up/Down is punched by default and will work fine if a simple one filament print is used. There is also the possibility (and recommended if you have the possibility) to print the texts with a contrasting color to make it more readable. Please view the [thingiverse pages](https://www.thingiverse.com/thing:6952547) for more information.

There are two LED slots for lighting the **Ignitron** label on the case. The following approach is suggested. The LEDs can be powered from the +5V pin on the ESP32 which is fed from USB power. Solder a wire to +5V and to one of the GND pins and put the two LEDs in series with a 47 ohm resistor (suitable for 5mm  red, yellow or green). Note that blue leds do not work here since they have to high forward voltage drop. 
The suggested approach is to use the J1 connector (if the PCB is used) that is unused since we instead power directly from USB. The J1 connector is already connected to +5V and GND.

### Optional dedicated Preset LEDs 
The case also has mounting sockets for 4 extra dedicated preset LEDs. To *enable this optional functionality in the firmware please see the related section under the source Readme*. If enabled it also *modifies* the behaviour of **Ignatron** to light up the FX LEDs for the selected preset instead of displaying the FX symbols in the OLED display. This way it is easy to see which Preset slot is used and exactly which FX pedals that are in use as each of them are lit by its own LED. If choosing not to use this optional functionality then just leave those extra sockets empty.

The LEDs has no connections on the PCB as this is a new addition to the functionality. Instead you need to solder the wires for the LEDs directly to the bare pins on the ESP32 board. The wires need to have the LED and a 470 ohm resistor in series. Make sure to use heat shrinkable tubes where approriate so not to short out anything. Each LED needs a connection to a GPIO pin + LED + resistor and then to ground. Make sure to connect the cathod leg to ground otherwise the LED will not light up.

|Preset slot| GPIO|
|-----------|-----|
|          1|    0|
|          2|    4|
|          3|   12|
|          4|   15|    

#### Hardware (BOM)
The printed 3D case uses the same ESP32 board as the orginal design above. Same foot switches and same LEDs for the FX pedal sockets. In addition there are two extra 5 mm green LEDs (for the IGNITRON label) these are connected in series with one 47 ohm 1/4W resistor. Four yellow 5 mm LEDs for the preset LEDs and four 470 ohm 1/4W resistors (optional)).
The OLED display is replaced by a larger SH1106 1.3" 128x64 i2C OLED.

The orginal enclosure, LED holder, USB jack and OLED frame are not used with the 3D printed case.

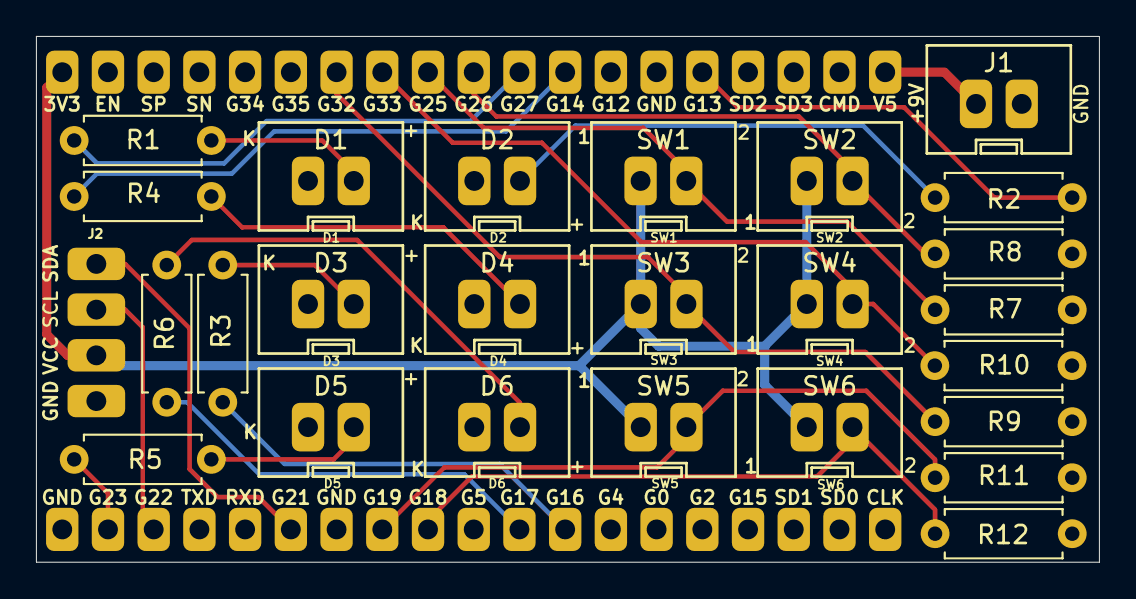
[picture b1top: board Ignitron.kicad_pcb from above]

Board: 2 copper layers, 59.1 x 29.2 mm, 27 parts (1 on the bottom side), 23 nets.

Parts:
D1, D2, D3, D4, D5, D6: LED; Conn_Socket_LED
IC1: ESP32-Pinout
J1: PowerIn; Conn_Socket_Power
J2: SSD_1306
R1: R_P1; R_Axial_DIN0207_L6.3mm_D2.5mm_P7.62mm_Horizontal
R2: R_P2; R_Axial_DIN0207_L6.3mm_D2.5mm_P7.62mm_Horizontal
R3: R_P3; R_Axial_DIN0207_L6.3mm_D2.5mm_P7.62mm_Horizontal
R4: R_P4; R_Axial_DIN0207_L6.3mm_D2.5mm_P7.62mm_Horizontal
R5: R_BD; R_Axial_DIN0207_L6.3mm_D2.5mm_P7.62mm_Horizontal
R6: R_BU; R_Axial_DIN0207_L6.3mm_D2.5mm_P7.62mm_Horizontal
R7, R8, R9, R10, R11, R12: 1K; R_Axial_DIN0207_L6.3mm_D2.5mm_P7.62mm_Horizontal
SW1: SW_P1DRV; Conn_Socket_Switch
SW2: SW_P2MOD; Conn_Socket_Switch
SW3: SW_P3DLY; Conn_Socket_Switch
SW4: SW_P4REV; Conn_Socket_Switch
SW5: SW_BDNG; Conn_Socket_Switch
SW6: SW_BUCOM; Conn_Socket_Switch

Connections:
+3V3: IC1.20, J2.2, SW1.1, SW2.1, SW3.1, SW4.1, SW5.1, SW6.1
+5V: IC1.38, J1.1
/G13: IC1.34, R2.1
/G14: IC1.31, R4.1
/G16: IC1.12, R3.1
/G17: IC1.11, R6.1
/G18: IC1.9, R12.1, SW6.2
/G19: IC1.8, R11.1, SW5.2
/G21: IC1.6, J2.4
/G22: IC1.3, J2.3
/G23: IC1.2, R5.1
/G25: IC1.28, R7.1, SW1.2
/G26: IC1.29, R8.1, SW2.2
/G27: IC1.30, R1.1
/G32: IC1.26, R9.1, SW3.2
/G33: IC1.27, R10.1, SW4.2
GND: D1.1, D2.1, D3.1, D4.1, D5.1, D6.1, IC1.1, IC1.7, IC1.33, J1.2, J2.1, R7.2, R8.2, R9.2, R10.2, R11.2, R12.2
unnamed: D1.2, R1.2
unnamed: D2.2, R2.2
unnamed: D3.2, R3.2
unnamed: D4.2, R4.2
unnamed: D5.2, R5.2
unnamed: D6.2, R6.2

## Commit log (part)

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2021-09-03 rename to Sparky.ino
2021-09-03 fixed bug when change to same preset of different bank did switch drive
2021-09-06 new name, new logo
2021-09-06 renamed project files
2021-09-06 changed Readme.md
2021-09-07 Final switch of GPIOs to match PCB design
2021-09-11 implemented Looper mode, Ignitron can now act as a keyboard
2021-09-14 Looper mode and some documentation
2021-09-15 update, many things open right now, unclear if branch will be continued
2021-09-15 Removed some debug log, changed looper switch to button 3
2021-09-15 moved files to src folder
2021-09-15 moved images to resources folder
2021-10-10 bugfix for incorrect JSON when preset was received from APP
2021-10-13 added OTA support and fixed Bluetooth issues
2021-10-18 fixed Looper keyboard behaviour(?)
2021-10-20 Ignitron pictures
2021-10-20 Update issue templates
2021-10-27 Updated firmware version
2021-10-27 added information material for hardware
2021-11-26 added Common.h
2021-11-26 cleaned up debug messages
2021-11-26 further investigation into bugfix
2021-11-28 initial setup to send license key (for enabling purchased packs?)
    - not working, maybe other messages have to be sent?
2021-11-28 added new debug messages
2021-12-27 unpatched BleKeyboard class by extracting added start/end methods to inheriting class
2021-12-31 Update DireStraitsnicemidrockto.json, PresetList.txt and one other file
2022-02-02 fixed bug where in some cases rounding errors can lead to incorrect FX pedal settings
2022-04-13 init preset repeatedly when not successful, update to latest libraries
2022-04-16 First try BT classic
2022-04-16 test
2022-04-17 log BT messages
2022-04-17 fixed ack msg to include sub_cmd, fixed double file name bug in AMP mode
2022-04-17 fixed ack message to include sub_cmd, fixed bug with double file names in AMP mode
2022-05-15 on the way to have both BT types running...
2022-07-13 fixed issue with AMP mode connection to App
2022-07-13 changed checkup delay to from 1.5s to 2s
2022-07-14 only preset info missing
2022-07-15 refactored end_message to match specification, todo amp preset receive
    connection working with refactored message builder, receiving presets
    not working
2022-07-17 code cleanup and harmonization
2022-08-15 fix newline while reading preset file
2022-08-15 use arduino 1.0.6 like sloeber does
2022-08-23 same from other directory
2023-01-02 Fixed issue with preset name in display in AMP mode
2023-01-02 switched to BLE mode as default
2023-01-02 some debug messages for received presets
2023-03-05 changed button config for looper mode, keyboard presses are not sent to device yet
2023-03-07 fixed looper function by removing pointer to spark_dc
2023-03-08 fixed mode persistence after BT change. TODO server fixing
2023-03-08 log incoming messages
2023-03-08 finally fixed all three modes. (Reason was keyboard MAC setting should only happen in APP mode)
2023-03-08 Implemented proper Looper mode
2023-03-10 added missing pdf for UV print
2023-03-16 File got accidentally deleted, readded
2023-03-17 small refactoring (removal of pointers)
2023-03-19 switched keyboard only/Looper buttons to 1-6 (short) and A-F (long)
2023-03-19 added display information for Keyboard only mode
2023-03-22 small bugfix to remove delay while deinitializing BLE keyboard
2023-03-23 renamed doxygen folder to documentation
2023-04-07 refactored SparkLEDControl and SparkButtonHandler to shift logic to SparkDataControl
2023-04-07 added connection status for Serial BT (AMP mode)
2023-04-07 fixed LED states for AMP mode, minor bugfixes, some refactoring
2023-04-08 increased speed of Serial BT connection
2023-04-28 fixed crash with empty preset from FS
2023-05-20 Delete data_old directory
    replaced with new data directory (recovered)
2023-06-29 still checkingg
2023-06-30 First try to set the intial preset to a non-HW one. TODO: Avoid HW presets if in Mini and GO mode
2023-07-25 delay after setting HW preset - not sure if required
2023-08-30 Removed legacy files for Credentials and updated Readme.md
2024-01-04 Added acknowledgment processing for cmd type 05
2024-01-04 Added handling to ignore HW bank for Spark Mini, needs to be reverted when going to MAIN
2024-01-06 minor cahnge to ack behavior
2024-01-06 Small fixes
2024-01-07 Adjusting debug log messages.
2024-01-08 added getCurrentPreset after changing presets
2024-01-10 added delay (50ms) for sending BT messages over BLE for stable operations
2024-01-12 fixes for preset change process (HW and custom)
2024-01-12 small fix on acknowledgments
2024-01-14 cleaned up handling of incomplete messages and resetting lastMessageType.
2024-01-14 switching Preset number after successfull preset change
2024-01-16 Fixed AMP mode overwriting received preset
2024-01-24 changed keyboard mapping to send special key and modificators, also repeating the key press
2024-02-03 Improved BT Keyboard with special keys and modifiers enabled. Fixed display issue from pull request
2024-02-11 removing ignore block when multi chunk message does not end with F7. (Might not work in all cases)
2024-02-12 adding support for different keyboard layouts in keyboard mode.
2024-02-13 Added multiple keyboard support for keyboard only mode.
2024-02-24 Changed message behavior to put incoming data into a queue for parallel processing
2024-02-25 Changed message queueing. Code cleanup required.
2024-02-25 Further cleanup
2024-02-26 disabled DEBUG mode
2024-02-26 disable debug
2024-02-27 BT messages shorter for Spark GO
2024-02-27 Automatic switch between Spark 40 and GO/Mini message format
2024-02-28 code cleanup and restructuring
2024-02-29 Fixed issue when Spark sometimes sends a preset change instead of an ACK
    which caused an inconsistent state
2024-03-01 Version update to 1.6.0
2024-03-08 Code cleanup in SparkStreamReader
2024-03-11 caching HW presets in the beginning, increased stability
2024-03-11 caching HW presets, increased stability
2024-03-12 Fixed code style and best practice
2024-03-12 fixed performance (initializer lists)
2024-03-14 test with HW init removed
2024-03-14 Add Codacy badge
2024-03-15 Code cleanup via codacy, implementation of HW preset caching to increase performance
2024-03-15 code cleanup (codacy)
2024-03-15 stabilized init routine (caching)
2024-03-17 tried to switch presets in app with Ignitron (AMP mode), seems not supported
2024-03-18 first tests
2024-09-06 fixed message processing for AMP mode
2024-09-06 fixed issue with pending preset on HW preset (toggle effect)
2024-09-06 fixed messasge block building for AMP mode
2024-09-07 fixed JSON parsing error when reading BPM
2024-09-07 changed recommendation to use PlatformIO
2024-09-08 fixed messaging to Spark Amp
2024-09-14 Changed message behavior
    - wait for acks on multi chunk messages before sending next chunk.
    - implemented splitting BLE messages into smaller units (needs cleanup)
2024-09-15 implemented message size
2024-09-15 desctivated debug msgs
2024-09-17 trying to get AMP mode for Spark 2 running
2024-09-17 added TODO
2024-09-20 added reading of looper settings
2024-09-21 added Looper config mode
2024-09-22 added SparkLooperTimer
2024-09-22 SparkLooperTimer continued
2024-09-24 implemetation of Spark 2 Looper controls
2024-09-24 adding more looper commands and process
2024-09-24 enabled debug messages
2024-09-25 further implementation of looper
2024-09-25 fixed conflicts
2024-10-02 Fixes on beat timer and buttons
2024-10-02 changed behavior to keep track of pending requests (mostly relevant for Looper commands)
2024-10-02 Fixed play/stop behavior
2024-10-10 n changed pins
2024-10-17 download_fs
2024-10-27 changed pedd pin
2024-11-14 reset looper beat count when stopping first recording in between
2024-11-18 ingore logs
2024-11-18 delete
2025-01-03 Switch to last preset on startup
2025-01-03 intermediate, change to read current setting when starting
2025-01-04 first sorting of DataControl methods, need to be extracted
2025-01-06 Switch to current preset in AMP when connecting.
2025-01-11 change to current amp preset on startup, load missing HW presets in background
2025-01-14 backup of chaanged pins
2025-01-21 add battery indicator
2025-01-23 Fix bug: when Spark disconnected, the battery indicator switch to low voltage symbol
2025-01-26 update docs
2025-01-27 Added LED lights to tuner, stability improvement on BT connection
2025-01-27 Addd Tuner info to Readme
2025-01-27 fixed switching off tuner on amp
2025-01-28 reverted SPIFFS.begin(true) until further investigation
2025-01-29 updated version to 1.7.4
2025-01-30 switch to LittleFS
2025-02-01 add bottom dynamic note offset in tuner
2025-02-02 disabled debug messages
2025-02-02 removed offset number
2025-02-02 version number increase
2025-02-05 caching HW presets in file system for faster startup
2025-02-06 unknown
2025-02-06 removed IDE files
2025-02-06 removed TODO comment
2025-02-06 version increase
2025-02-06 enabled hw checksums for Spark2
2025-02-07 enabled Spark 2 extended HW presets
2025-02-07 Updated info on library versions
2025-02-10 Add SH1106 OLED driver. Add 4 extra dedicated preset LEDs. Updated Readme in src and hardware.
2025-02-12 pull request 46
2025-02-12 Version update
2025-02-13 fixed bug with tuner status switch
2025-02-17 in progress
2025-02-17 Added Thingiverse links and 3D case pictures.
2025-02-19 increased version
2025-02-20 Activated defines for SH1106 OLED and 4 dedicated prweset LEDs.
2025-03-09 added battery level display for amp battery
2025-03-11 changing battery symbol when charging
2025-03-11 reduced delay for reading missing HW presets
2025-03-11 added plug symbol for wall powered devices
2025-03-11 calculated battery levels for amp battery
2025-03-11 fixed bug on define for battery levels
2025-03-15 refactor: replace #define with const for preset edit constants and improve method signatures
2025-03-22 refactor: changed const/defines to enum
2025-03-22 Replaced further defines with enum
2025-03-22 cleaned up enums
2025-03-23 adjusted battery levels for amp battery
2025-03-23 battery level adjustment
2025-03-24 Updated display bottom line to print centered and camel case. Added optional blink mode for FX modification mode. Fix bug of Tuner LEDs not displaying.
2025-03-26 Clean up preset names
2025-04-04 start load last preset on startup
2025-04-04 update version number
2025-04-07 loading last preset on connection based on preset number
2025-04-27 Support SH1107
2025-08-05 Refactor toggleFX method to eliminate redundant loops and improve readability
2025-08-27 moved files to module folders and fixed includes
2025-08-27 Reorder include statements to maintain consistency across header files
2025-08-27 Refactor SparkModeManager and SparkDataControl to improve readability and maintainability by removing redundant whitespace and adding access method for SparkModeManager.
2025-08-29 Ensure BatteryChargingStatus is always available
2025-08-30 Refactor SparkModeManager access across the codebase for improved clarity and direct usage, marking old delegation methods as deprecated. Update documentation and examples to reflect new access patte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
2025-08-30 Implement resetOpModeFile method in SparkModeManager and update restartESP logic in SparkDataControl to remove OpMode file, preventing fixed mode issues.
2025-08-31 Initialize BLE keyboard in KEYBOARD mode within SparkHardwareManager
2025-08-31 .gitattributes aktualisieren
2025-09-01 Add setDataControl method to SparkBTControl and update hardware initialization in SparkHardwareManager
2025-09-01 Fixed BLE Keyboard by changing from pointer to object
2025-09-01 Refactor SparkBTControl and SparkDataControl to use references instead of pointers, improving memory management and code clarity. Update SparkHardwareManager to reflect these changes and enhance BLE 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
2025-09-06 Add ifndef statements in Spark_Namespace.h to ensure proper header guard structure
2025-09-06 platformio.ini aktualisieren
    Fixed incorrect partition setting
2025-09-10 Refactor code structure for improved readability and maintainability
